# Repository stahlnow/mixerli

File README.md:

# mixerli

Battery powered 10 channel (4x2 + 1x2) stereo mixer featuring stereo input level control slider and stereo rotary aux send level control.

# Documentation

* [Build guide](documentation/build_guide.pdf)
* [Schematics](documentation/schematics/v2.0/mixerli_schematics_v2.0.1.pdf)

# License

SPDX-FileCopyrightText: 2023 Stahl office@stahlnow.com
SPDX-License-Identifier: CERN-OHL-S-2.0+

This source describes Open Hardware and is licensed under the CERN-OHL-S v2
or any later version.

You may redistribute and modify this source and make products using it
under the terms of the CERN-OHL-S v2 or any later version
(https://ohwr.org/cern_ohl_s_v2.txt).

This source is distributed WITHOUT ANY EXPRESS OR IMPLIED
WARRANTY, INCLUDING OF MERCHANTABILITY, SATISFACTORY
QUALITY AND FITNESS FOR A PARTICULAR PURPOSE. Please see
the CERN-OHL-S v2 for applicable conditions.

Source location: https://github.com/stahlnow/mixerli

As per CERN-OHL-S v2 section 4, should You produce hardware based
on this source, You must where practicable maintain the Source Location
visible on the printed circuit board of the mixerli or other products you make using this source.

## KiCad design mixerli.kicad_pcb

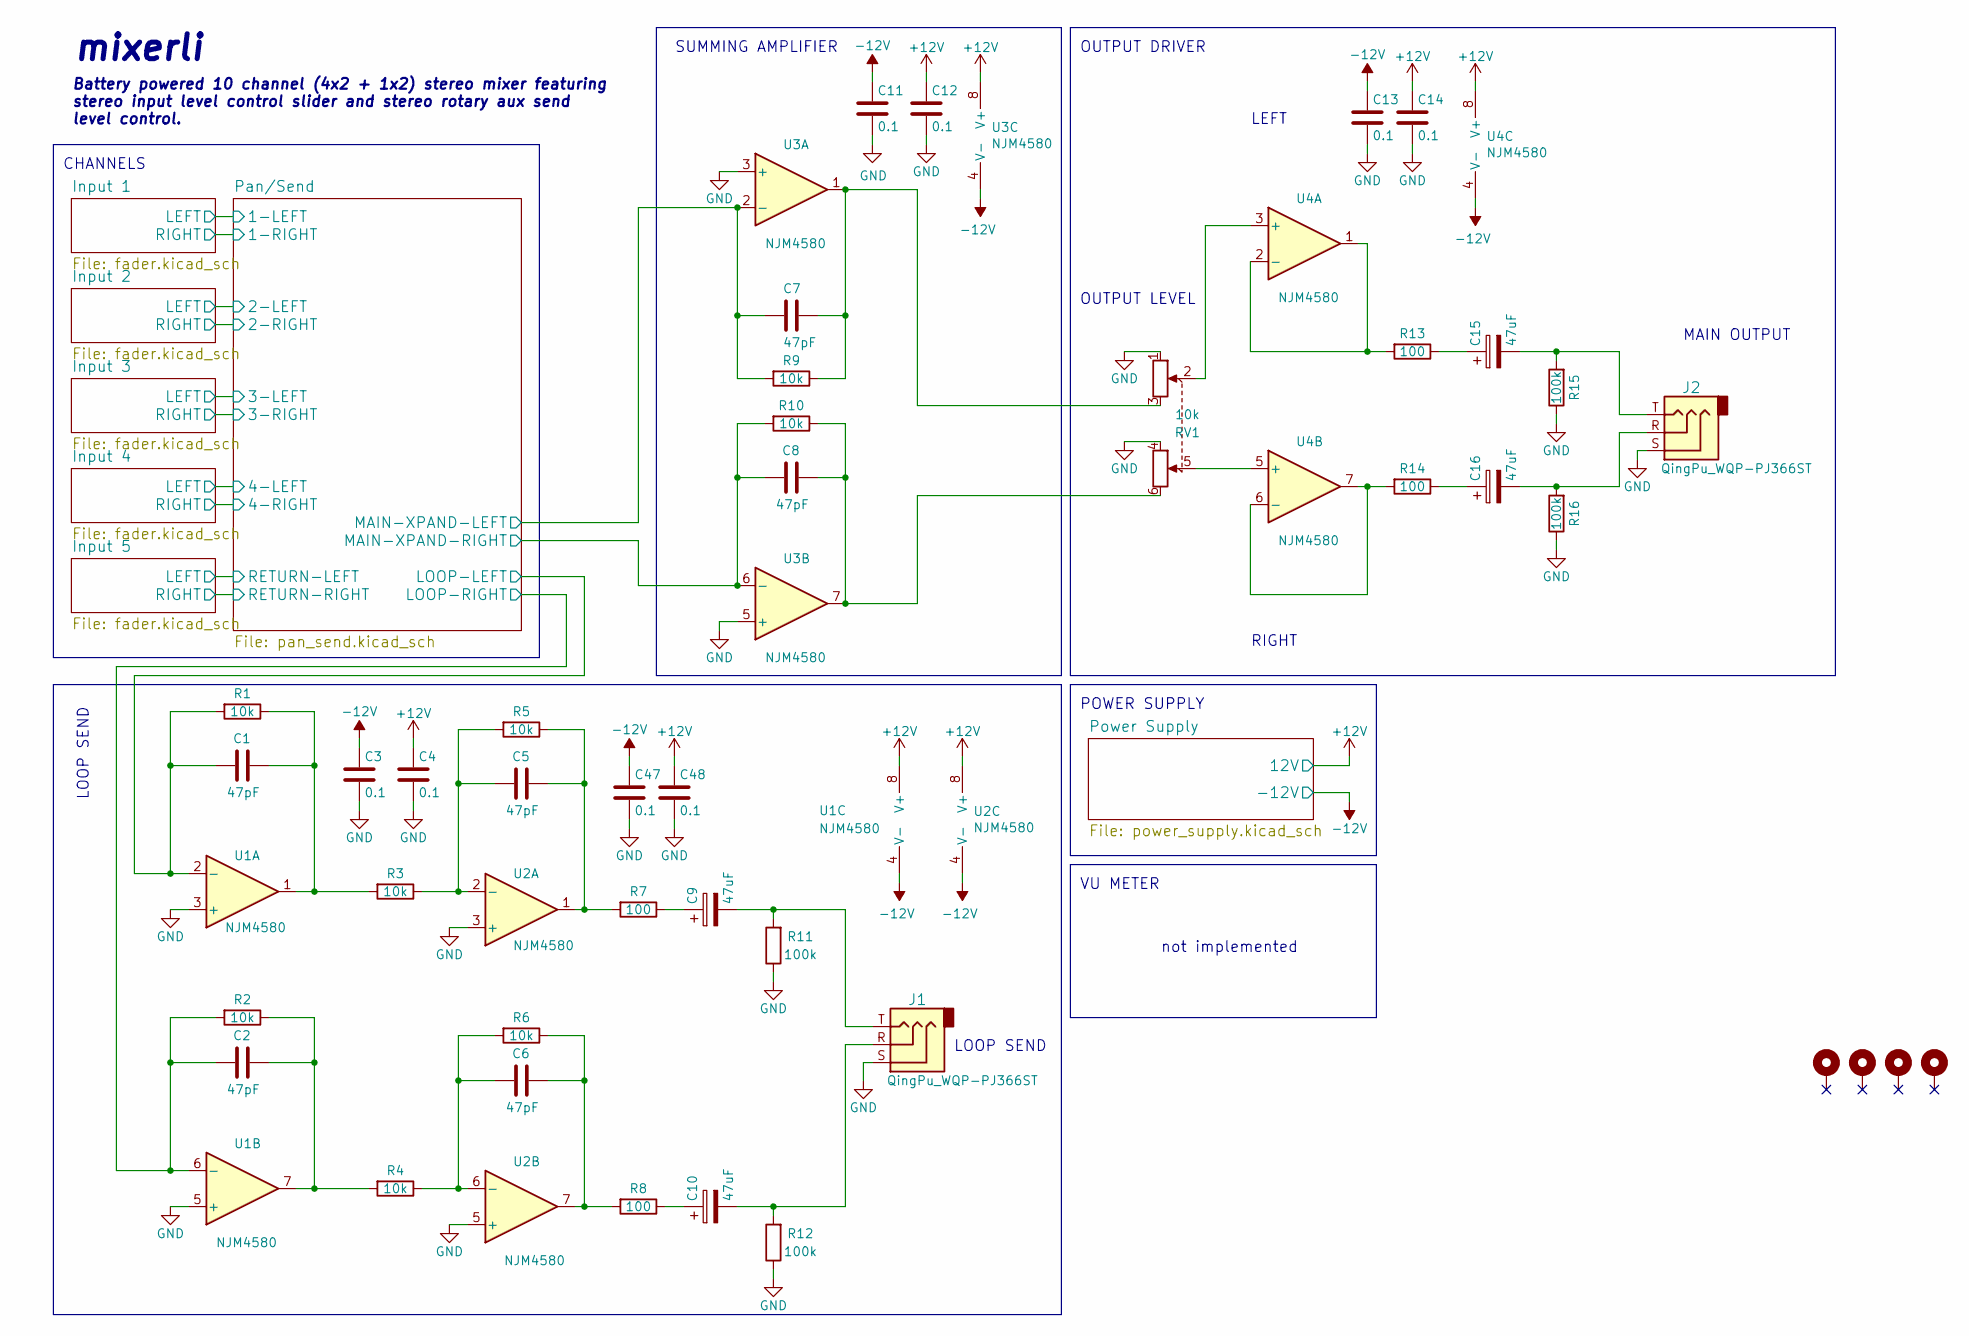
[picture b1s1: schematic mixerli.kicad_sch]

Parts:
C1, C2, C5, C6, C7, C8: 47pF; C_1206_3216Metric
C3, C4, C11, C12, C13, C14, C47, C48: 0.1; C_1206_3216Metric
C9, C10, C15, C16: 47uF; CP_Elec_5x5.8
H1, H2, H3, H4: MountingHole_Pad; MountingHole_3mm_Pad
J1, J2: QingPu_WQP-PJ366ST; Jack_3.5mm_QingPu_WQP-PJ366ST_Vertical
R1, R2, R3, R4, R5, R6, R9, R10: 10k; R_1206_3216Metric
R7, R8, R13, R14: 100; R_1206_3216Metric
R11, R12, R15, R16: 100k; R_1206_3216Metric
RV1: 10k; RS451121400A
U1, U2, U3, U4: NJM4580; SOIC-8_3.9x4.9mm_P1.27mm

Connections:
+12V: C4.1, C12.1, C14.1, C48.1, U1.8 (V+), U2.8 (V+), U3.8 (V+), U4.8 (V+); also elsewhere on the board
-12V: C3.1, C11.1, C13.1, C47.1, U1.4 (V-), U2.4 (V-), U3.4 (V-), U4.4 (V-); also elsewhere on the board
/Pan/Send/LOOP-LEFT: C1.1, R1.2, U1.2 (-); also elsewhere on the board
/Pan/Send/LOOP-RIGHT: C2.1, R2.2, U1.6 (-); also elsewhere on the board
/Pan/Send/MAIN-XPAND-LEFT: C7.2, R9.2, U3.2 (-); also elsewhere on the board
/Pan/Send/MAIN-XPAND-RIGHT: C8.1, R10.2, U3.6 (-); also elsewhere on the board
GND: C3.2, C4.2, C11.2, C12.2, C13.2, C14.2, C47.2, C48.2, J1.S, J2.S, R11.1, R12.1, R15.1, R16.1, RV1.1, RV1.4, U1.3 (+), U1.5 (+), U2.3 (+), U2.5 (+), U3.3 (+), U3.5 (+); also elsewhere on the board
unnamed: C1.2, R1.1, R3.2, U1.1
unnamed: C2.2, R2.1, R4.2, U1.7
unnamed: C5.2, R5.1, R7.2, U2.1
unnamed: C6.2, R6.1, R8.2, U2.7
unnamed: C7.1, R9.1, RV1.3, U3.1
unnamed: C8.2, R10.1, RV1.6, U3.7
unnamed: C9.1, R7.1
unnamed: C9.2, J1.T, R11.2
unnamed: C10.1, R8.1
unnamed: C10.2, J1.R, R12.2
unnamed: C15.1, R13.1
unnamed: C15.2, J2.T, R15.2
unnamed: C16.1, R14.1
unnamed: C16.2, J2.R, R16.2
unnamed: C5.1, R3.1, R5.2, U2.2 (-)
unnamed: C6.1, R4.1, R6.2, U2.6 (-)
unnamed: RV1.2, U4.3 (+)
unnamed: R13.2, U4.1, U4.2 (-)
unnamed: RV1.5, U4.5 (+)
unnamed: R14.2, U4.6 (-), U4.7

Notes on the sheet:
SUMMING AMPLIFIER
CHANNELS
not implemented
LOOP SEND
OUTPUT LEVEL
mixerli
POWER SUPPLY
VU METER
RIGHT
MAIN OUTPUT
OUTPUT DRIVER
LEFT
Battery powered 10 channel (4x2 + 1x2) stereo mixer featuring stereo input level control slider and stereo rotary aux send level control.

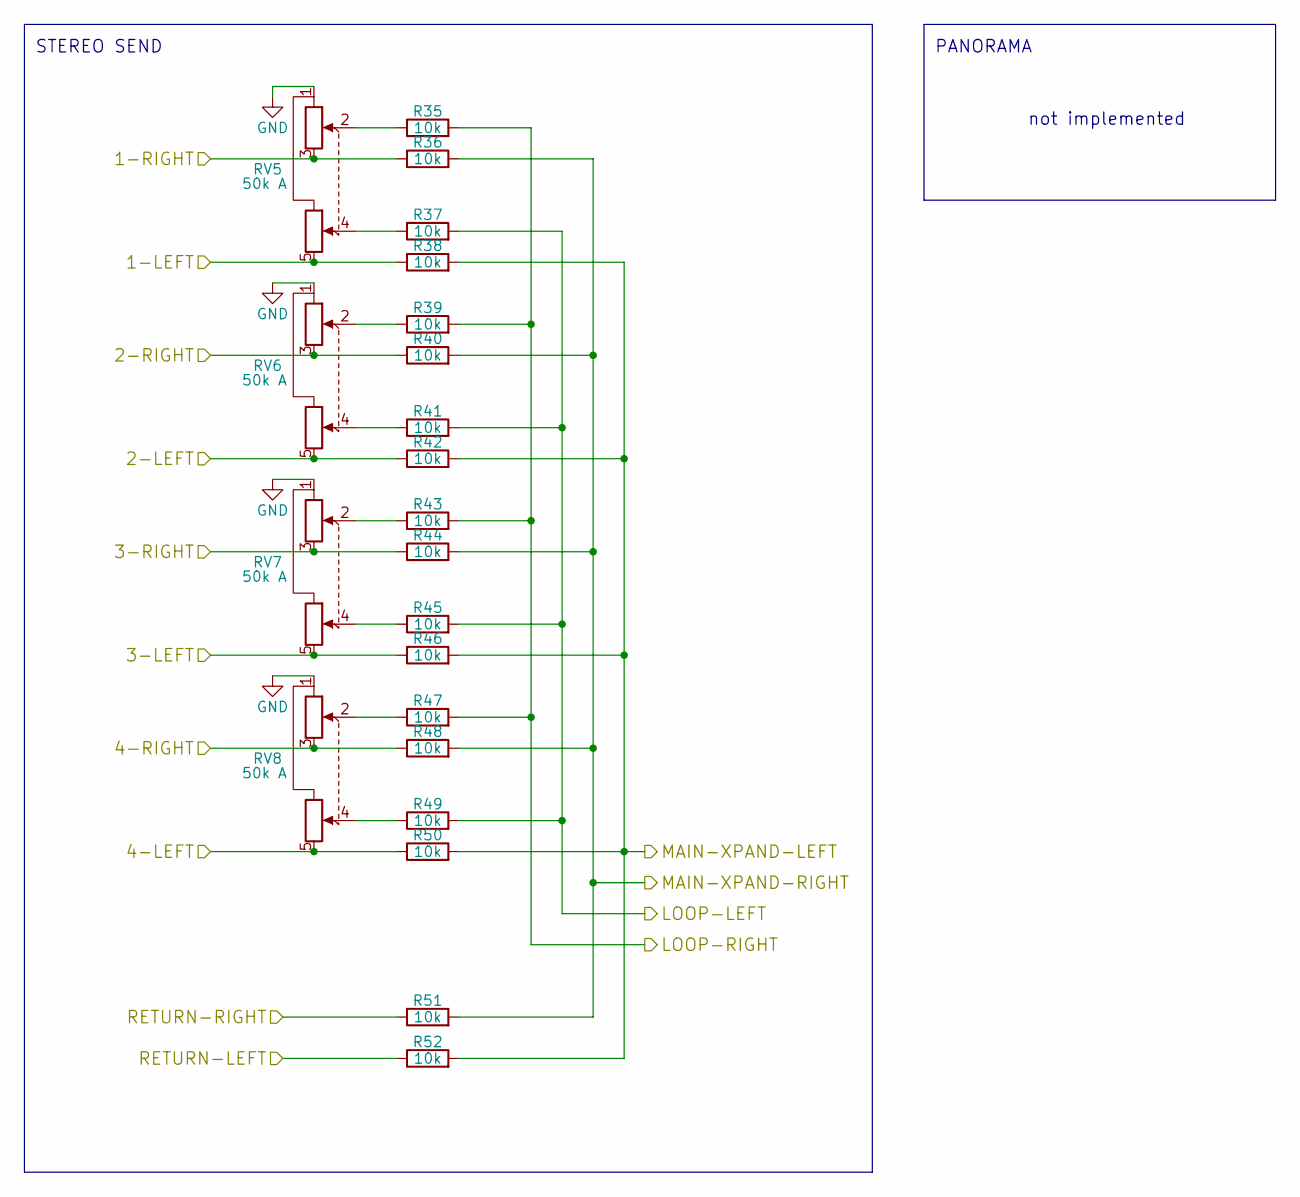
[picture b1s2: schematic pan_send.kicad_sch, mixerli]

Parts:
R35, R36, R37, R38, R39, R40, R41, R42, R43, R44, R45, R46, R47, R48, R49, R50, R51, R52: 10k; R_1206_3216Metric
RV5, RV6, RV7, RV8: 50k A; RK14K12D0A18

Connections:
/Input 1/LEFT: R38.1, RV5.5; also elsewhere on the board
/Input 1/RIGHT: R36.1, RV5.3; also elsewhere on the board
/Input 2/LEFT: R42.1, RV6.5; also elsewhere on the board
/Input 2/RIGHT: R40.1, RV6.3; also elsewhere on the board
/Input 3/LEFT: R46.1, RV7.5; also elsewhere on the board
/Input 3/RIGHT: R44.1, RV7.3; also elsewhere on the board
/Input 4/LEFT: R50.1, RV8.5; also elsewhere on the board
/Input 4/RIGHT: R48.1, RV8.3; also elsewhere on the board
/Input 5/LEFT: R52.1; also elsewhere on the board
/Input 5/RIGHT: R51.1; also elsewhere on the board
/Pan/Send/LOOP-LEFT: R37.2, R41.2, R45.2, R49.2; also elsewhere on the board
/Pan/Send/LOOP-RIGHT: R35.2, R39.2, R43.2, R47.2; also elsewhere on the board
/Pan/Send/MAIN-XPAND-LEFT: R38.2, R42.2, R46.2, R50.2, R52.2; also elsewhere on the board
/Pan/Send/MAIN-XPAND-RIGHT: R36.2, R40.2, R44.2, R48.2, R51.2; also elsewhere on the board
GND: RV5.1, RV6.1, RV7.1, RV8.1; also elsewhere on the board
unnamed: R35.1, RV5.2
unnamed: R37.1, RV5.4
unnamed: R39.1, RV6.2
unnamed: R41.1, RV6.4
unnamed: R43.1, RV7.2
unnamed: R45.1, RV7.4
unnamed: R47.1, RV8.2
unnamed: R49.1, RV8.4

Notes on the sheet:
STEREO SEND
not implemented
PANORAMA

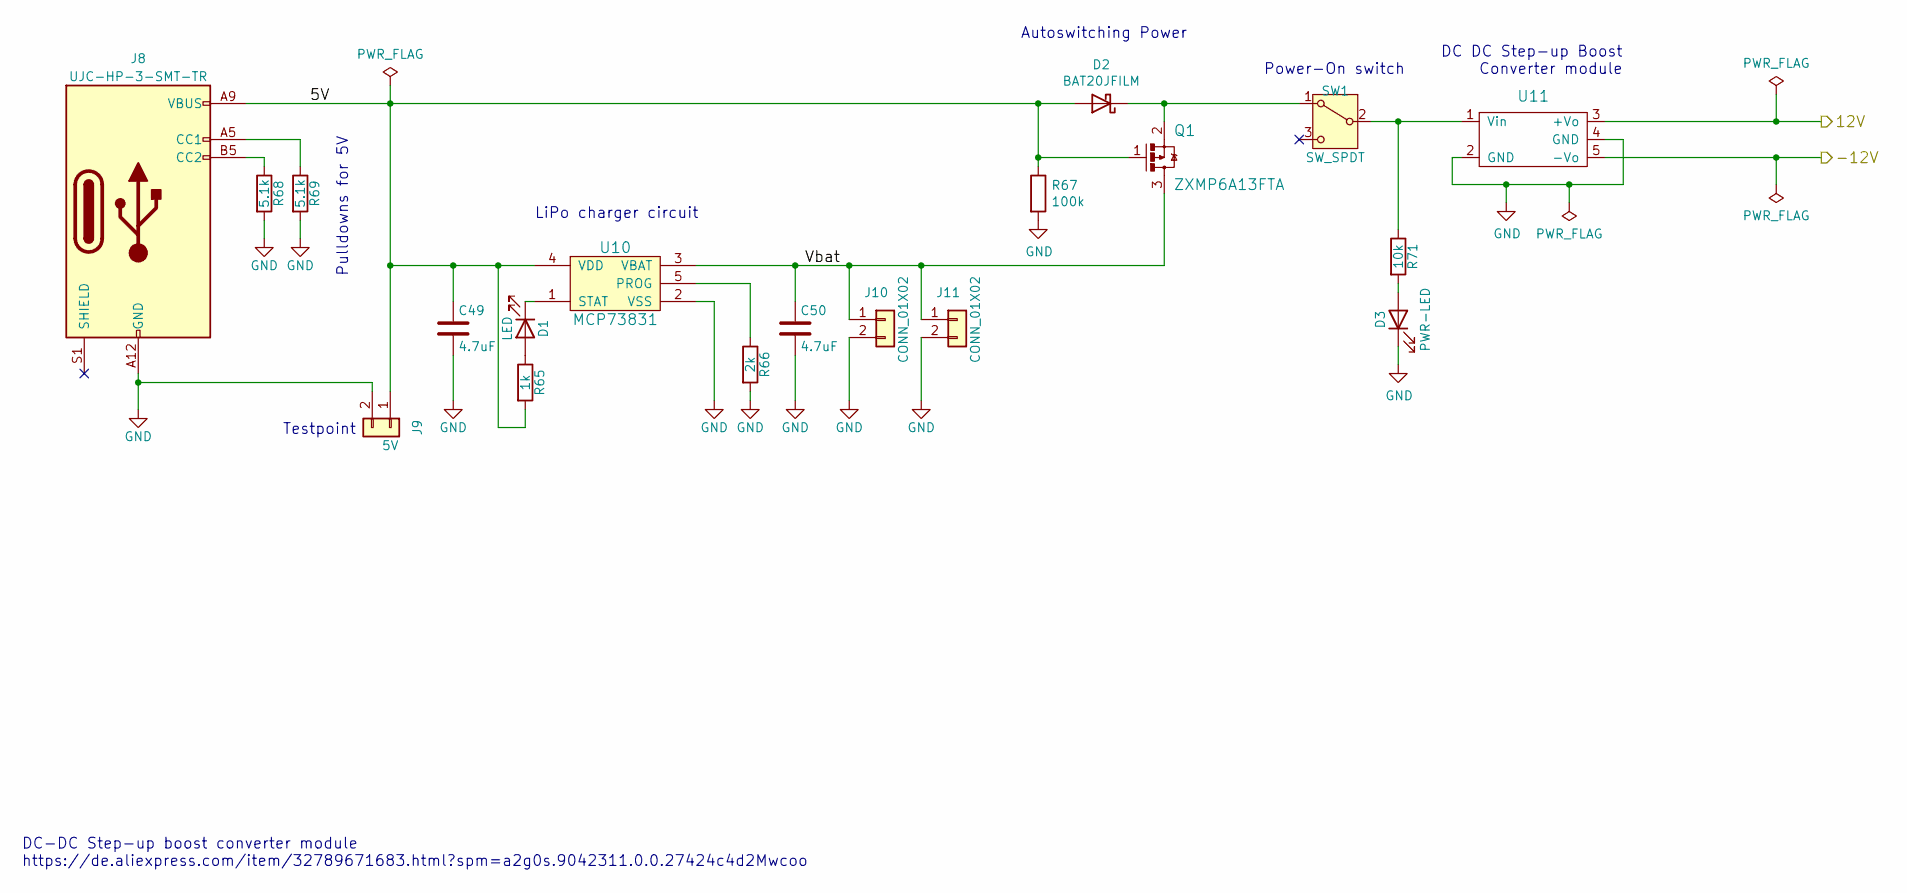
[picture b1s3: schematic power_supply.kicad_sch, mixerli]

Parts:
C49, C50: 4.7uF; C_1206_3216Metric
D1: LED; LED_Rectangular_W5.0mm_H2.0mm
D2: BAT20JFILM; D_SOD-323
D3: PWR-LED; LED_Rectangular_W5.0mm_H2.0mm
J8: UJC-HP-3-SMT-TR; USB_C_Receptacle_CUI_Devices_UJC-HP-3-SMT-TR
J9: 5V; PinHeader_1x02_P2.54mm_Vertical
J10: CONN_01X02; JST_PH_S2B-PH-K_1x02_P2.00mm_Horizontal
J11: CONN_01X02; PinHeader_1x02_P2.54mm_Vertical
Q1: ZXMP6A13FTA; SOT-23
R65: 1k; R_1206_3216Metric
R66: 2k; R_1206_3216Metric
R67: 100k; R_1206_3216Metric
R68, R69: 5.1k; R_1206_3216Metric
R71: 10k; R_1206_3216Metric
SW1: SW_SPDT; Switches_Alps_SSSS916400
U10: MCP73831; SOT-23-5
U11: DC-DC-Boost-Converter-Positive-Negative-Dual-Outp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; DC-DC-Boost-Converter-Positive-Negative-Dual-Output-Power-S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

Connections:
+12V: U11.3 (+Vo); also elsewhere on the board
-12V: U11.5 (-Vo); also elsewhere on the board
/Power Supply/5V: C49.1, D2.2 (A), J8.A9 (VBUS), J8.B9 (VBUS), J9.1, Q1.1, R65.2, R67.1, U10.4 (VDD)
/Power Supply/Vbat: C50.1, J10.1, J11.1, Q1.3, U10.3 (VBAT)
GND: C49.2, C50.2, D3.1 (K), J8.A12 (GND), J8.B12 (GND), J9.2, J10.2, J11.2, R66.2, R67.2, R68.2, R69.2, U10.2 (VSS), U11.2 (GND), U11.4 (GND); also elsewhere on the board
unnamed: D1.2 (A), R65.1
unnamed: D1.1 (K), U10.1 (STAT)
unnamed: D2.1 (K), Q1.2, SW1.1 (A)
unnamed: D3.2 (A), R71.2
unnamed: J8.A5 (CC1), R69.1
unnamed: J8.B5 (CC2), R68.1
unnamed: R71.1, SW1.2 (B), U11.1 (Vin)
unnamed: R66.1, U10.5 (PROG)

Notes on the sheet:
DC-DC Step-up boost converter module https://de.aliexpress.com/item/32789671683.html?spm=a2g0s.9042311.0.0.27424c4d2Mwcoo
Autoswitching Power
Testpoint
Power-On switch
Pulldowns for 5V
DC DC Step-up Boost Converter module
LiPo charger circuit

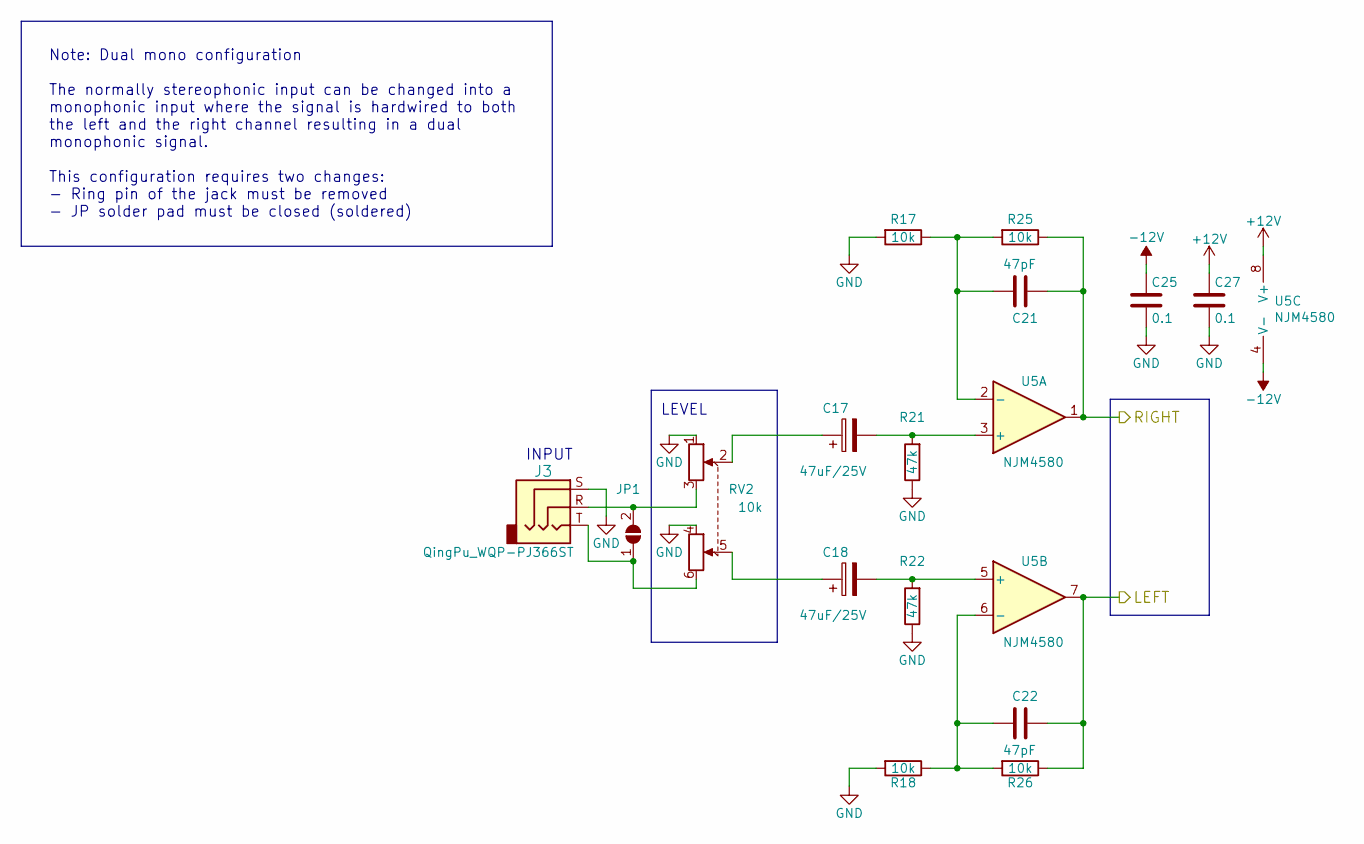
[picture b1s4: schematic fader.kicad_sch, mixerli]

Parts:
C17, C18: 47uF/25V; CP_Elec_5x5.8
C21, C22: 47pF; C_1206_3216Metric
C25, C27: 0.1; C_1206_3216Metric
J3: QingPu_WQP-PJ366ST; Jack_3.5mm_QingPu_WQP-PJ366ST_Vertical
JP1: SolderJumper_2_Open; SolderJumper-2_P1.3mm_Open_TrianglePad1.0x1.5mm
R17, R18, R25, R26: 10k; R_1206_3216Metric
R21, R22: 47k; R_1206_3216Metric
RV2: 10k; RS451121400A
U5: NJM4580; SOIC-8_3.9x4.9mm_P1.27mm

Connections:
+12V: C27.1, U5.8 (V+); also elsewhere on the board
-12V: C25.1, U5.4 (V-); also elsewhere on the board
/Input 1/LEFT: C22.1, R26.1, U5.7; also elsewhere on the board
/Input 1/RIGHT: C21.1, R25.1, U5.1; also elsewhere on the board
GND: C25.2, C27.2, J3.S, R17.2, R18.2, R21.1, R22.1, RV2.1, RV2.4; also elsewhere on the board
unnamed: C17.1, RV2.2
unnamed: C18.1, RV2.5
unnamed: J3.T, JP1.1 (A), RV2.6
unnamed: J3.R, JP1.2 (B), RV2.3
unnamed: C17.2, R21.2, U5.3 (+)
unnamed: C21.2, R17.1, R25.2, U5.2 (-)
unnamed: C18.2, R22.2, U5.5 (+)
unnamed: C22.2, R18.1, R26.2, U5.6 (-)

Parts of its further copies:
C19, C20, C29, C30, C35, C36, C41, C42: 47uF/25V; CP_Elec_5x5.8
C23, C24, C31, C32, C37, C38, C43, C44: 47pF; C_1206_3216Metric
C26, C28, C33, C34, C39, C40, C45, C46: 0.1; C_1206_3216Metric
J4, J5, J6, J7: QingPu_WQP-PJ366ST; Jack_3.5mm_QingPu_WQP-PJ366ST_Vertical
JP2, JP3, JP4, JP5: SolderJumper_2_Open; SolderJumper-2_P1.3mm_Open_TrianglePad1.0x1.5mm
R19, R20, R27, R28, R29, R30, R33, R34, R53, R54, R57, R58, R59, R60, R63, R64: 10k; R_1206_3216Metric
R23, R24, R31, R32, R55, R56, R61, R62: 47k; R_1206_3216Metric
RV3, RV4, RV9, RV10: 10k; RS451121400A
U6, U7, U8, U9: NJM4580; SOIC-8_3.9x4.9mm_P1.27mm

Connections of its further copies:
+12V: C28.1, C34.1, C40.1, C46.1, U6.8 (V+), U7.8 (V+), U8.8 (V+), U9.8 (V+); also elsewhere on the board
-12V: C26.1, C33.1, C39.1, C45.1, U6.4 (V-), U7.4 (V-), U8.4 (V-), U9.4 (V-); also elsewhere on the board
/Input 2/LEFT: C24.1, R28.1, U6.7; also elsewhere on the board
/Input 2/RIGHT: C23.1, R27.1, U6.1; also elsewhere on the board
/Input 3/LEFT: C32.1, R34.1, U7.7; also elsewhere on the board
/Input 3/RIGHT: C31.1, R33.1, U7.1; also elsewhere on the board
/Input 4/LEFT: C38.1, R58.1, U8.7; also elsewhere on the board
/Input 4/RIGHT: C37.1, R57.1, U8.1; also elsewhere on the board
/Input 5/LEFT: C44.1, R64.1, U9.7; also elsewhere on the board
/Input 5/RIGHT: C43.1, R63.1, U9.1; also elsewhere on the board
GND: C26.2, C28.2, C33.2, C34.2, C39.2, C40.2, C45.2, C46.2, J4.S, J5.S, J6.S, J7.S, R19.2, R20.2, R23.1, R24.1, R29.2, R30.2, R31.1, R32.1, R53.2, R54.2, R55.1, R56.1, R59.2, R60.2, R61.1, R62.1, RV3.1, RV3.4, RV4.1, RV4.4, RV9.1, RV9.4, RV10.1, RV10.4; also elsewhere on the board
unnamed: C19.1, RV3.2
unnamed: C20.1, RV3.5
unnamed: C29.1, RV4.2
unnamed: C30.1, RV4.5
unnamed: C35.1, RV9.2
unnamed: C36.1, RV9.5
unnamed: C41.1, RV10.2
unnamed: C42.1, RV10.5
unnamed: J4.T, JP2.1 (A), RV3.6
unnamed: J4.R, JP2.2 (B), RV3.3
unnamed: J5.T, JP3.1 (A), RV4.6
unnamed: J5.R, JP3.2 (B), RV4.3
unnamed: J6.T, JP4.1 (A), RV9.6
unnamed: J6.R, JP4.2 (B), RV9.3
unnamed: J7.T, JP5.1 (A), RV10.6
unnamed: J7.R, JP5.2 (B), RV10.3
unnamed: C19.2, R23.2, U6.3 (+)
unnamed: C23.2, R19.1, R27.2, U6.2 (-)
unnamed: C20.2, R24.2, U6.5 (+)
unnamed: C24.2, R20.1, R28.2, U6.6 (-)
unnamed: C29.2, R31.2, U7.3 (+)
unnamed: C31.2, R29.1, R33.2, U7.2 (-)
unnamed: C30.2, R32.2, U7.5 (+)
unnamed: C32.2, R30.1, R34.2, U7.6 (-)
unnamed: C35.2, R55.2, U8.3 (+)
unnamed: C37.2, R53.1, R57.2, U8.2 (-)
unnamed: C36.2, R56.2, U8.5 (+)
unnamed: C38.2, R54.1, R58.2, U8.6 (-)
unnamed: C41.2, R61.2, U9.3 (+)
unnamed: C43.2, R59.1, R63.2, U9.2 (-)
unnamed: C42.2, R62.2, U9.5 (+)
unnamed: C44.2, R60.1, R64.2, U9.6 (-)

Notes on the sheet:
INPUT
LEVEL
Note: Dual mono configuration The normally stereophonic input can be changed into a monophonic input where the signal is hardwired to both the left and the right channel resulting in a dual monophonic signal. This configuration requires two changes: - Ring pin of the jack must be removed - JP solde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

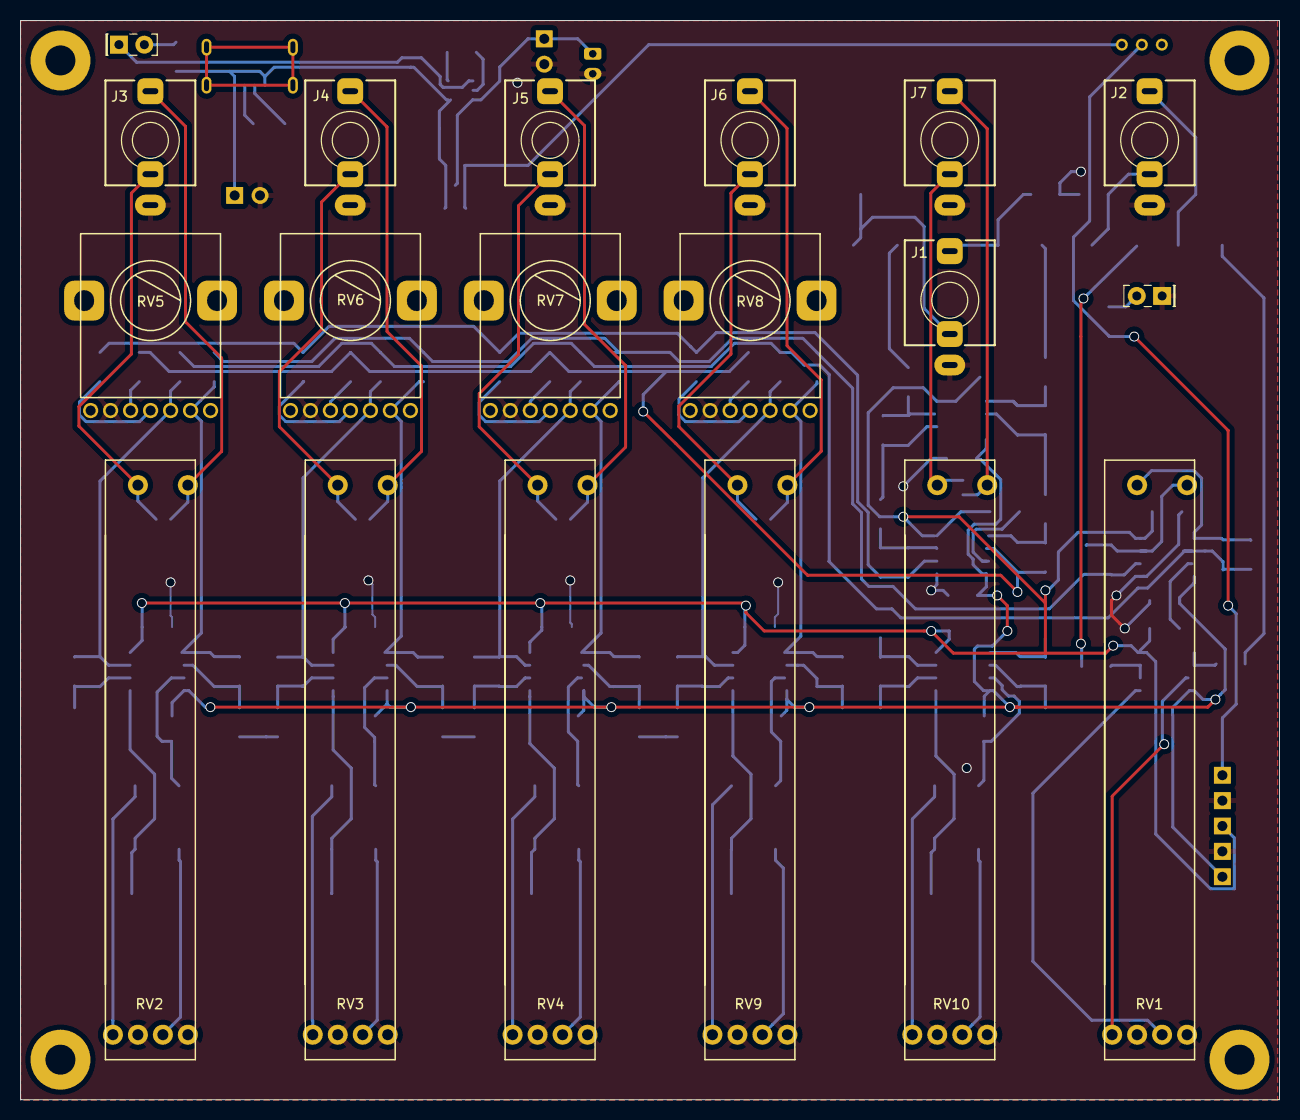
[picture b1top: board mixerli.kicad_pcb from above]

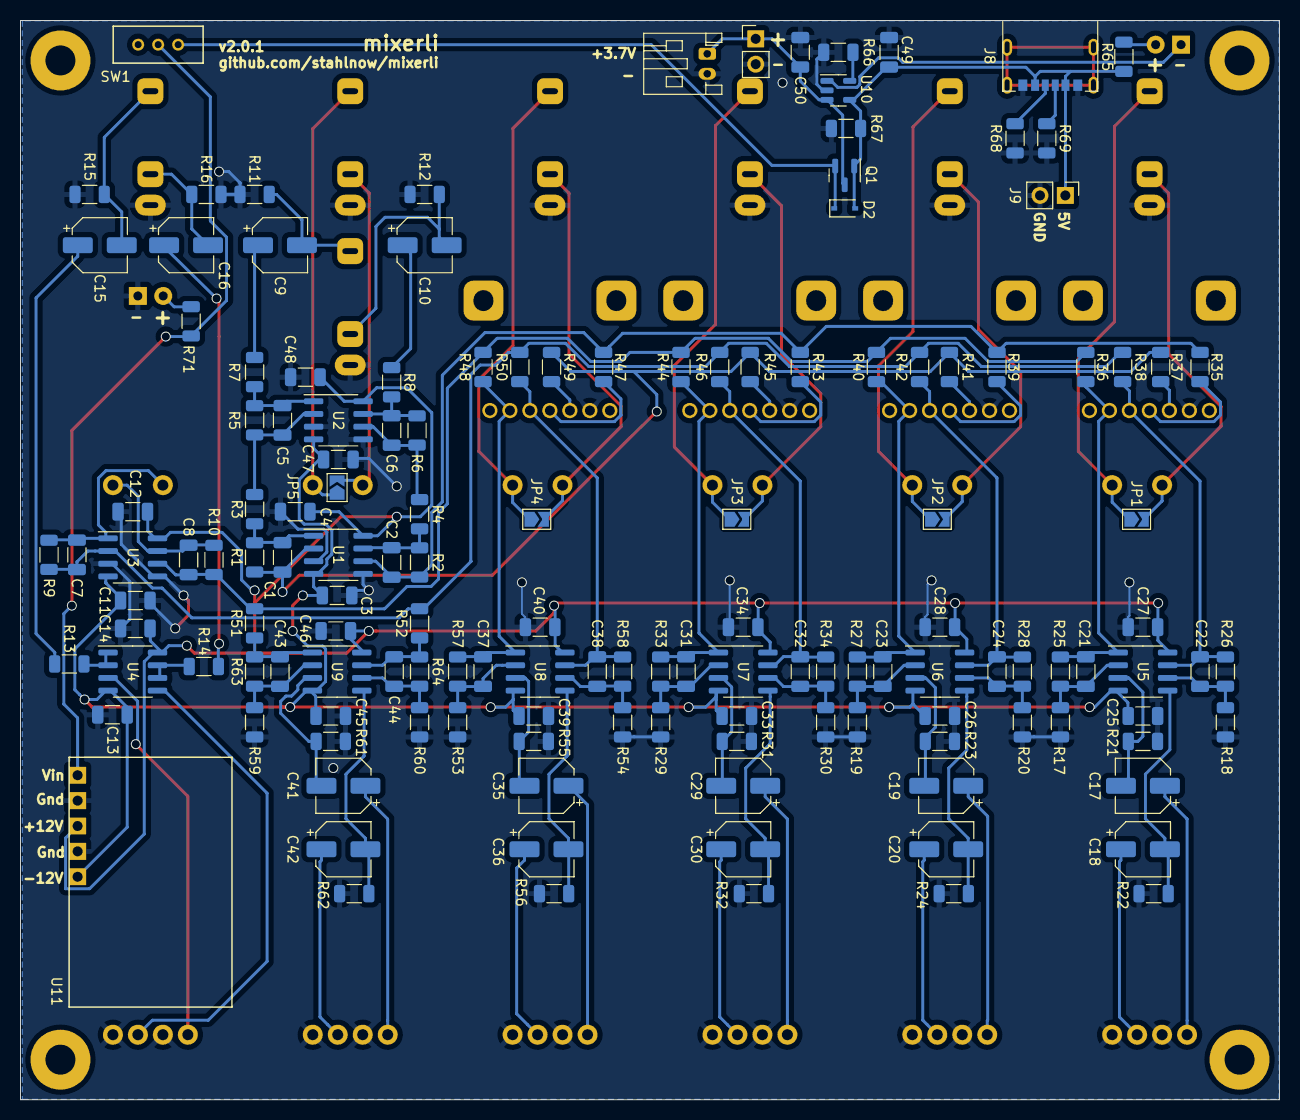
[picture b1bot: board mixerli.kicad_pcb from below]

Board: 2 copper layers, 126.0 x 108.0 mm, 166 parts (143 on the bottom side), 95 nets.

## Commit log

2018-02-25 :rocket: take off
2019-01-27 update to kicad version 5, bug fix layout
2022-04-05 :rocket: 2.0.0
2022-05-26 holes, jst bat, ..
2022-08-25 mixerli 2.0.0 alpha
2023-05-13 documentation / update kicad
2023-05-13 add screenshot
2023-05-13 link to build guide and schematics
2023-06-30 dev, bkp
2023-06-30 *.bkp
2023-06-30 backups
2023-06-30 CERN-OHL-S v2
2023-06-30 update license, ..
2023-06-30 update LICENSE
2023-06-30 tidy up..
2023-07-02 gerber 2.0.0 final
2023-07-02 remove bkp file
2023-07-02 layout postscript
2023-07-03 fix potentiometer holes NPTH -> through hole
2023-08-11 added erratum for pull-down resistors
2023-08-11 case update
2023-08-11 datasheets
2023-08-11 backups, move 3d stuff
2024-08-06 v2.0.1: fixed pulldown resistors
2024-08-06 fix link
2024-08-06 gerber v2.0.1
2024-12-24 metal sheet enclosure for 2.0 (charge led cutout missing!)
2026-01-07 backup
2026-01-07 metalsheet enclosure
2026-01-07 kicad 9

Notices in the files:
fader.kicad_sch:
Copyright 2023 stahl. Licensed under CERN- OHL-S v2 or any later version.
